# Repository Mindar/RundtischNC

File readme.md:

# Rundtisch NC
Rundtisch NC is a numerical control for indexing heads. It allows you to set a number of divisons using a rotary encoder and then drives the right distance on the push of a button.

*For international visitors: Unfortunately this repository is mostly in german. A notable exception to this is the firmware. In the future there might be a english version of the documentation, but for now there isn't one 😪*

[User manual / Bedienungsanleitung 🇩🇪 (.pdf)](./doc/bedienungsanleitung.pdf)

## License
- Firmware: MIT
- Documentation, PCB layout, schematic, images: Creative Commons CC-BY (or MIT)

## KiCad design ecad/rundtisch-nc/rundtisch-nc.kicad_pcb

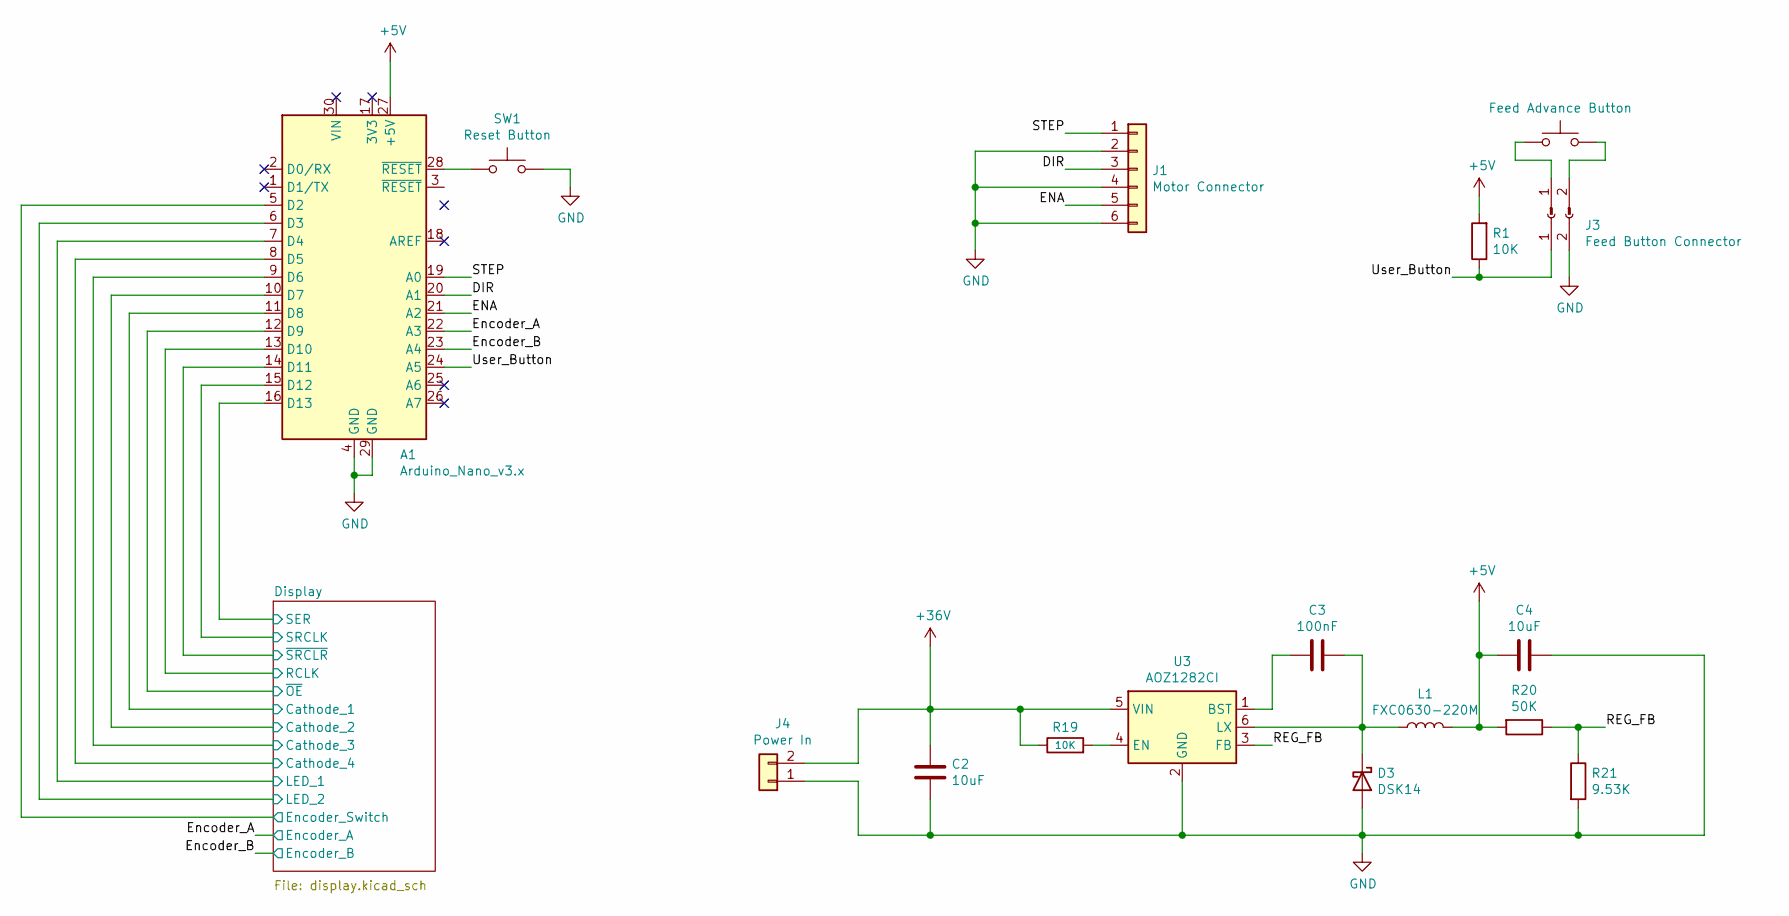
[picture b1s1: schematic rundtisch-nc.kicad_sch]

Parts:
A1: Arduino_Nano_v3.x; Arduino_Nano
C2, C4: 10uF; C_0805_2012Metric_Pad1.18x1.45mm_HandSolder
C3: 100nF; C_0603_1608Metric_Pad1.08x0.95mm_HandSolder
D3: DSK14; D_SOD-123
J1: Motor Connector; WJ15EDGRC-3.81-6P
J2: Feed Advance Stecker
J3: Feed Button Connector; WJ15EDGRC-3.81-2P
J4: Power In; WJ15EDGRC-3.81-2P
L1: FXC0630-220M
R1, R19: 10K; R_0603_1608Metric_Pad0.98x0.95mm_HandSolder
R20: 50K; R_0603_1608Metric_Pad0.98x0.95mm_HandSolder
R21: 9.53K; R_0603_1608Metric_Pad0.98x0.95mm_HandSolder
SW1: Reset Button; WJ15EDGRC-3.81-2P
SW2: Feed Advance Button; WJ15EDGRC-3.81-2P
U3: AOZ1282CI; SOT-23-6

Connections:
+5V: A1.27 (+5V), C4.1, L1.2, R1.2, R20.2; also elsewhere on the board
+36V: C2.1, J4.2, R19.1, U3.5 (VIN)
/DIR: A1.20 (A1), J1.3
/Display/Cathode_1: A1.11 (D8); also elsewhere on the board
/Display/Cathode_2: A1.10 (D7); also elsewhere on the board
/Display/Cathode_3: A1.9 (D6); also elsewhere on the board
/Display/Cathode_4: A1.8 (D5); also elsewhere on the board
/Display/Encoder_Switch: A1.5 (D2); also elsewhere on the board
/Display/LED_1: A1.7 (D4); also elsewhere on the board
/Display/LED_2: A1.6 (D3); also elsewhere on the board
/Display/RCLK: A1.13 (D10); also elsewhere on the board
/Display/SER: A1.16 (D13); also elsewhere on the board
/Display/SRCLK: A1.15 (D12); also elsewhere on the board
/Display/~OE: A1.12 (D9); also elsewhere on the board
/Display/~SRCLR: A1.14 (D11); also elsewhere on the board
/ENA: A1.21 (A2), J1.5
/Encoder_A: A1.22 (A3); also elsewhere on the board
/Encoder_B: A1.23 (A4); also elsewhere on the board
/REG_FB: R20.1, R21.1, U3.3 (FB)
/STEP: A1.19 (A0), J1.1
/User_Button: A1.24 (A5), J3.1, R1.1
GND: A1.4 (GND), A1.29 (GND), C2.2, C4.2, D3.2 (A), J1.2, J1.4, J1.6, J3.2, J4.1, R21.2, SW1.2, U3.2 (GND); also elsewhere on the board
unnamed: C3.1, U3.1 (BST)
unnamed: C3.2, D3.1 (K), L1.1, U3.6 (LX)
unnamed: J2.1, SW2.1
unnamed: J2.2, SW2.2
unnamed: R19.2, U3.4 (EN)
unnamed: A1.28 (~RESET), SW1.1

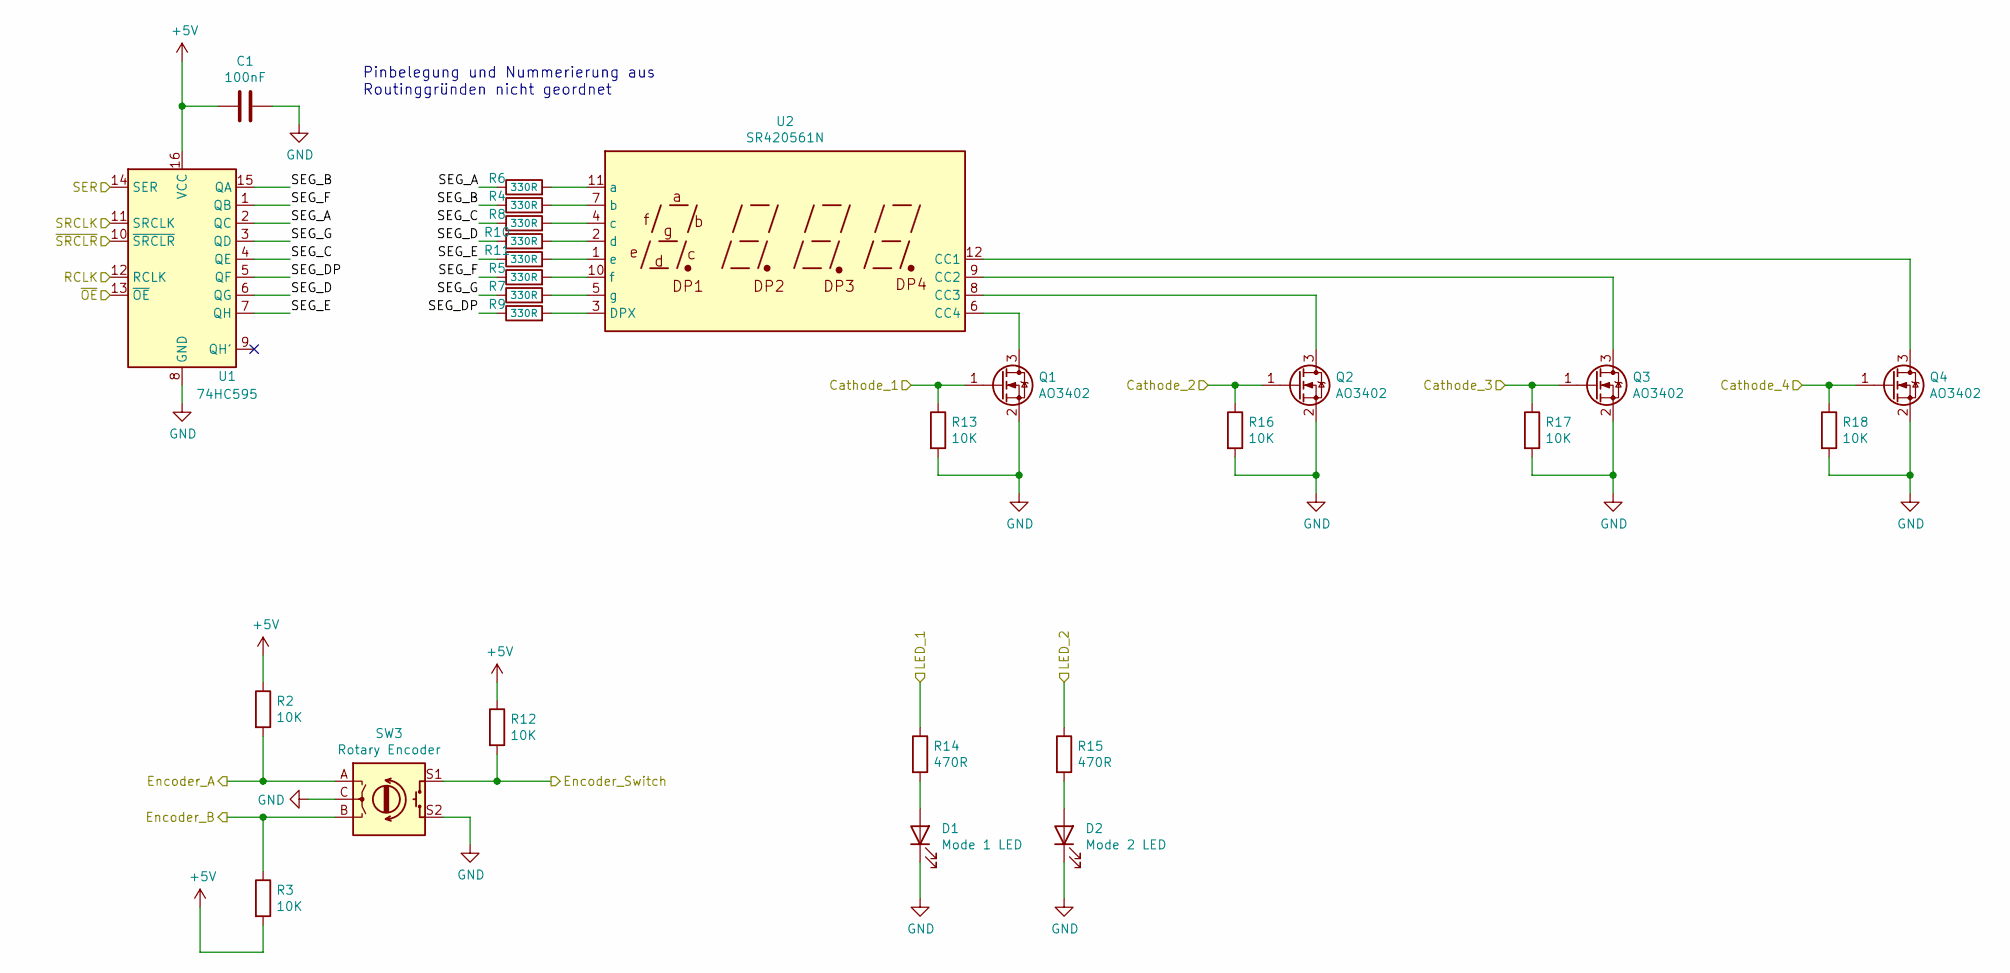
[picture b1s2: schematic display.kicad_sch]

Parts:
C1: 100nF; C_0603_1608Metric_Pad1.08x0.95mm_HandSolder
D1: Mode 1 LED; LED_0805_2012Metric_Pad1.15x1.40mm_HandSolder
D2: Mode 2 LED; LED_0805_2012Metric_Pad1.15x1.40mm_HandSolder
Q1, Q2, Q3, Q4: AO3402; SOT-23_Handsoldering
R2, R3, R12, R13, R16, R17, R18: 10K; R_0603_1608Metric_Pad0.98x0.95mm_HandSolder
R4, R5, R6, R7, R8, R9, R10, R11: 330R; R_0603_1608Metric_Pad0.98x0.95mm_HandSolder
R14, R15: 470R; R_0603_1608Metric_Pad0.98x0.95mm_HandSolder
SW3: Rotary Encoder; RotaryEncoder_Alps_EC11E-Switch_Vertical_H20mm
U1: 74HC595; SOIC-16_3.9x9.9mm_P1.27mm
U2: SR420561N

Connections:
+5V: C1.1, R2.1, R3.2, R12.1, U1.16 (VCC); also elsewhere on the board
/Display/Cathode_1: Q1.1 (G), R13.1; also elsewhere on the board
/Display/Cathode_2: Q2.1 (G), R16.1; also elsewhere on the board
/Display/Cathode_3: Q3.1 (G), R17.1; also elsewhere on the board
/Display/Cathode_4: Q4.1 (G), R18.1; also elsewhere on the board
/Display/Encoder_Switch: R12.2, SW3.S1; also elsewhere on the board
/Display/LED_1: R14.1; also elsewhere on the board
/Display/LED_2: R15.1; also elsewhere on the board
/Display/RCLK: U1.12 (RCLK); also elsewhere on the board
/Display/SEG_A: R6.1, U1.2 (QC)
/Display/SEG_B: R4.1, U1.15 (QA)
/Display/SEG_C: R8.1, U1.4 (QE)
/Display/SEG_D: R10.1, U1.6 (QG)
/Display/SEG_DP: R9.1, U1.5 (QF)
/Display/SEG_E: R11.1, U1.7 (QH)
/Display/SEG_F: R5.1, U1.1 (QB)
/Display/SEG_G: R7.1, U1.3 (QD)
/Display/SER: U1.14 (SER); also elsewhere on the board
/Display/SRCLK: U1.11 (SRCLK); also elsewhere on the board
/Display/~OE: U1.13 (~OE); also elsewhere on the board
/Display/~SRCLR: U1.10 (~SRCLR); also elsewhere on the board
/Encoder_A: R2.2, SW3.A; also elsewhere on the board
/Encoder_B: R3.1, SW3.B; also elsewhere on the board
GND: C1.2, D1.1 (K), D2.1 (K), Q1.2 (S), Q2.2 (S), Q3.2 (S), Q4.2 (S), R13.2, R16.2, R17.2, R18.2, SW3.C, SW3.S2, U1.8 (GND); also elsewhere on the board
unnamed: D1.2 (A), R14.2
unnamed: D2.2 (A), R15.2
unnamed: Q1.3 (D), U2.6 (CC4)
unnamed: Q2.3 (D), U2.8 (CC3)
unnamed: Q3.3 (D), U2.9 (CC2)
unnamed: Q4.3 (D), U2.12 (CC1)
unnamed: R4.2, U2.7 (b)
unnamed: R5.2, U2.10 (f)
unnamed: R6.2, U2.11 (a)
unnamed: R7.2, U2.5 (g)
unnamed: R8.2, U2.4 (c)
unnamed: R9.2, U2.3 (DPX)
unnamed: R10.2, U2.2 (d)
unnamed: R11.2, U2.1 (e)

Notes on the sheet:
Pinbelegung und Nummerierung aus Routinggründen nicht geordnet

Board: 2 copper layers, 43 parts (6 on the bottom side), 48 nets, no tracks yet.

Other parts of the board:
SW1#2: Reset Button; WJ15EDGRC-3.81-2P

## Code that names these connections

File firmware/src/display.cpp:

#include <Arduino.h>
#include <TimerOne.h>
#include <stdio.h>

#include "display.hpp"

#define SEG_B 1 << 0
#define SEG_F 1 << 1
#define SEG_A 1 << 2
#define SEG_G 1 << 3
#define SEG_C 1 << 4
#define SEG_DP 1 << 5
#define SEG_D 1 << 6
#define SEG_E 1 << 7

#define CAT4 5
#define CAT3 6
#define CAT2 7
#define CAT1 8

#define SR_OUTPUT_ENABLE 9
#define SR_LATCH_CLOCK 10 // storage/latch clock
#define SR_RESET 11
#define SR_SHIFT_CLOCK 12
#define SR_SERIAL_DATA 13

char currentDigit = 3;
char displayText[5] = " Loc";


void displayOutput(){
	// Turn off old digit
	digitalWrite(CAT4 + currentDigit, HIGH);

	// Move to next digit
	currentDigit += 1;
	currentDigit = currentDigit >= 4 ? 0 : currentDigit;

	// Prepare latch clock
	digitalWrite(SR_LATCH_CLOCK, LOW);

	shiftOut(SR_SERIAL_DATA, SR_SHIFT_CLOCK, MSBFIRST, getSegments(displayText[((int)currentDigit)]));

	// Latch data and turn on new digit
	digitalWrite(SR_LATCH_CLOCK, HIGH);
	digitalWrite(CAT4 + currentDigit, LOW);
}

void setupDisplay(){
	pinMode(CAT4, OUTPUT);
	pinMode(CAT3, OUTPUT);
	pinMode(CAT2, OUTPUT);
	pinMode(CAT1, OUTPUT);

	pinMode(SR_OUTPUT_ENABLE, OUTPUT);
	pinMode(SR_LATCH_CLOCK, OUTPUT);
	pinMode(SR_RESET, OUTPUT);
	pinMode(SR_SHIFT_CLOCK, OUTPUT);
	pinMode(SR_SERIAL_DATA, OUTPUT);

	digitalWrite(SR_RESET, HIGH);
	digitalWrite(SR_OUTPUT_ENABLE, LOW);

	digitalWrite(SR_LATCH_CLOCK, LOW);
	digitalWrite(SR_SHIFT_CLOCK, LOW);
	digitalWrite(SR_SERIAL_DATA, LOW);


	// Turn off all digits
	digitalWrite(CAT1, HIGH);
	digitalWrite(CAT2, HIGH);
	digitalWrite(CAT3, HIGH);
	digitalWrite(CAT4, HIGH);

	Timer1.initialize(1000);
	Timer1.attachInterrupt(displayOutput);
	Timer1.start();
}

char getSegments(char character) {
	switch (character)
	{
		case '0':
			return SEG_A | SEG_B | SEG_C | SEG_D | SEG_E | SEG_F;
		case '1':
			return SEG_B | SEG_C;
		case '2':
			return SEG_A | SEG_B | SEG_G | SEG_E | SEG_D;
		case '3':
			return SEG_A | SEG_B | SEG_C | SEG_D | SEG_G;
		case '4':
			return SEG_F | SEG_B | SEG_C | SEG_G;
		case '5':
			return SEG_A | SEG_F | SEG_G | SEG_C | SEG_D;
		case '6':
			return SEG_A | SEG_F | SEG_G | SEG_C | SEG_D | SEG_E;
		case '7':
			return SEG_A | SEG_B | SEG_C;
		case '8':
			return SEG_A | SEG_B | SEG_C | SEG_D | SEG_E | SEG_F | SEG_G;
		case '9':
			return SEG_A | SEG_B | SEG_C | SEG_D | SEG_F | SEG_G;
		case 'A':
			return SEG_A | SEG_B | SEG_C | SEG_E | SEG_F | SEG_G;
		case 'b':
			return SEG_C | SEG_D | SEG_E | SEG_F | SEG_G;
		case 'C':
			return SEG_A | SEG_F | SEG_E | SEG_D;
		case 'd':
			return SEG_B | SEG_C | SEG_D | SEG_E | SEG_G;
		case 'E':
			return SEG_A | SEG_D | SEG_E | SEG_F | SEG_G;
		case 'F':
			return SEG_A | SEG_E | SEG_F | SEG_G;
		case 'L':
			return SEG_F | SEG_E | SEG_D;
		case 'o':
			return SEG_C | SEG_D | SEG_E | SEG_G;
		case 'c':
			return SEG_E | SEG_D | SEG_G;
		case 'H':
			return SEG_B | SEG_C | SEG_G | SEG_F | SEG_E;
		default:
			return 0x00;
	}
}

void setDisplayText(const char* text) {
	for(int i = 0; i < 4; i++) {
		displayText[i] = text[i];
	}
}

char* setDisplayNumber(int number) {
	if(number < 0 || number > 9999) {
		setDisplayText("FEHL");
	} else {
		sprintf(displayText, "%d", number);
	}

	return displayText;
}

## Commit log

2021-09-16 Changed info for international visitors in readme
2022-03-12 Simplified PCB Assembly by using internal Pullups
2022-03-12 Adjustments to max speed default
2023-10-26 added more images
